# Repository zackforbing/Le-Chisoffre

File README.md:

# Le-Chisoffre

chiff riff with trackpad, mouseball or rotary support, now with hotswap

don't get mad at me if these don't work, they are untested. I have zero idea what I'm doing, and your yolo to jlc is not my problem

7/21/25 case probably complete. still have to prototype though. and export/upload the files. but hey pretty pictures

original readme preserved below

## Layout

[Link](https://www.keyboard-layout-editor.com/##@_name=Le%20Chisoffre&author=Ha%20Ha%20Ha%3B&@_y:2.5&x:5.95&a:7&w:1.25&h:1.25%3B&=%3B&@_r:10&rx:1&y:-0.09999999999999998&x:2&a:4%3B&=E%3B&@_y:-0.65&x:1%3B&=W&_x:1%3B&=R&=T%3B&@_y:-0.75%3B&=Q%3B&@_y:-0.6&x:2%3B&=D%3B&@_y:-0.6499999999999999&x:1%3B&=S&_x:1%3B&=F&=G%3B&@_y:-0.75%3B&=A%3B&@_y:-0.6000000000000001&x:2%3B&=C%3B&@_y:-0.6499999999999999&x:1%3B&=X&_x:1%3B&=V&=B%3B&@_y:-0.75%3B&=Z%3B&@_y:-0.6000000000000001&x:2&a:7&h:1.25%3B&=%3B&@_y:-0.6499999999999999&x:3&h:1.25%3B&=%3B&@_y:0.25&x:5&c=%239cffb2&h:1.5%3B&=%3B&@_y:-0.75&x:4&h:1.25%3B&=%3B&@_r:100&rx:5.25&ry:4&y:-1.1&x:-0.20000000000000018&c=%23f59595&w:1.5&w2:1.25&h2:2&x2:0.25%3B&=%3B&@_r:-100&rx:7.25&ry:4.87&y:-0.3200000000000003&x:-0.5099999999999998&w:1.5&w2:1.25&h2:2%3B&=%3B&@_r:-10&rx:7&ry:0.965&y:-0.20499999999999996&x:2.25&c=%23cccccc&a:4%3B&=I%3B&@_y:-0.6499999999999999&x:1.25%3B&=U&_x:1%3B&=O%3B&@_y:-0.9900000000000002&x:0.25%3B&=Y%3B&@_y:-0.76&x:4.25%3B&=P%3B&@_y:-0.6000000000000003&x:2.25%3B&=K%3B&@_y:-0.6499999999999999&x:1.25%3B&=J&_x:1%3B&=L%3B&@_y:-0.9899999999999998&x:0.25%3B&=H%3B&@_y:-0.7600000000000002&x:4.25%3B&=%2F:%0A%2F%3B%3B&@_y:-0.6000000000000001&x:2.25%3B&=%3C%0A,%3B&@_y:-0.6399999999999997&x:0.25%3B&=N&=M&_x:1%3B&=%3E%0A.%3B&@_y:-0.75&x:4.25%3B&=%3F%0A%2F%2F%3B&@_y:-0.6200000000000001&x:2.25&a:7&h:1.25%3B&=%3B&@_y:-0.6299999999999999&x:1.25&h:1.25%3B&=%3B&@_y:0.22999999999999954&x:-0.75&c=%239cffb2&h:1.5%3B&=%3B&@_y:-0.75&x:0.25&h:1.25%3B&=)

## Todo

- [ ] order & test pcb
- [ ] create firmware
- [x] create case

## Disclaimer

Please note that this project is a work in progress with no guarantees of a working outcome. No-one involved in this project is responsible for any usage issues that may arise. However, feel free to edit, modify and otherwise utilise these files.

## License

This project is released under the GPL v3 License. Please refer to the LICENCE file.

## Credits

As always big thanks to the many people who helped me and inspired this board!

Any questions, contact Calvin0563 on Discord.

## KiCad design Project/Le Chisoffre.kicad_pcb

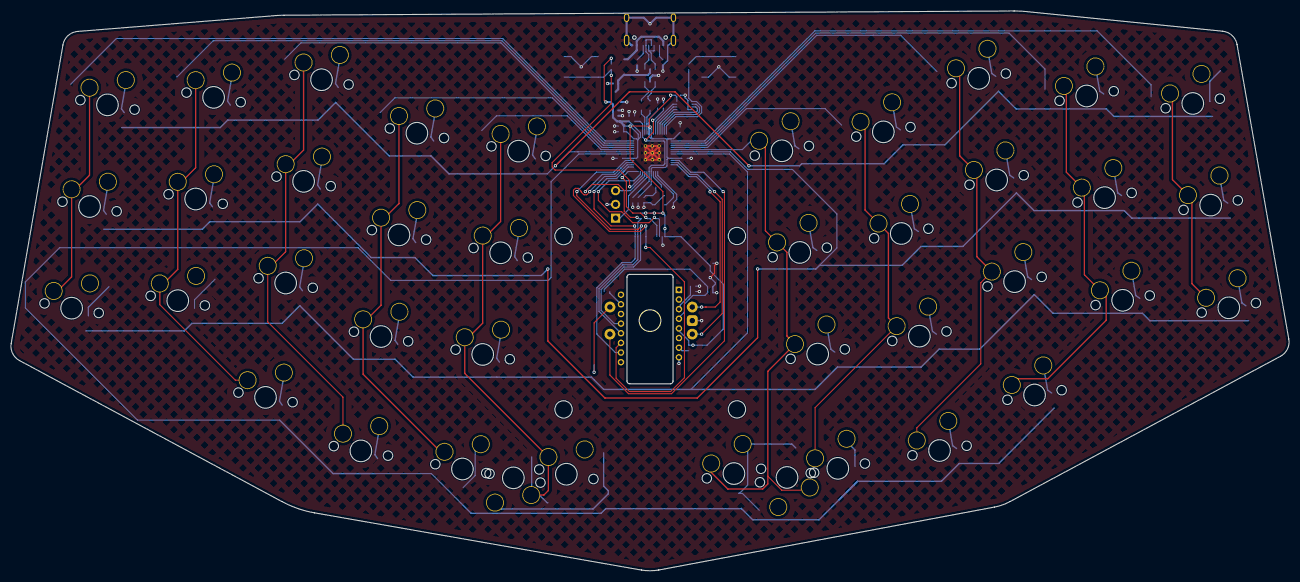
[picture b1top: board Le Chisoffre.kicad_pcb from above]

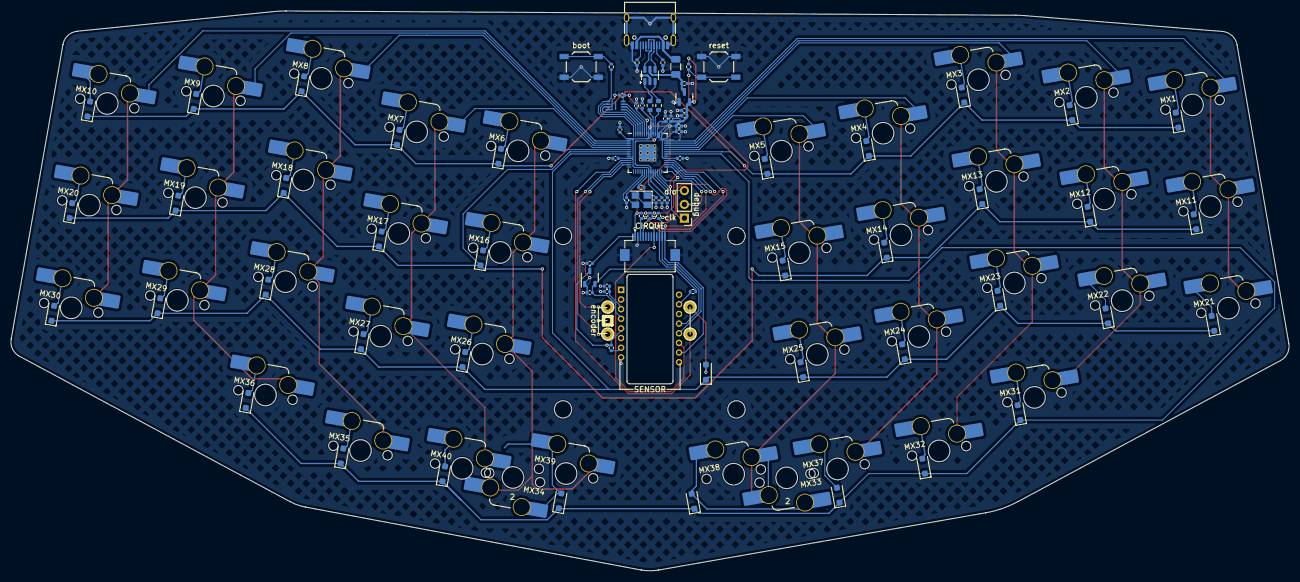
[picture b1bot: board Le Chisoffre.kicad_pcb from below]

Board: 2 copper layers, 235.8 x 103.3 mm, 130 parts (85 on the bottom side), 92 nets.

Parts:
C1, C5, C6, C9, C10, C11, C12, C13, C14, C15: 100nF; C_0402_1005Metric
C2, C3: 22pF; C_0402_1005Metric
C4, C8, C16, C17: 1uF; C_0402_1005Metric
C7: 10uF; C_0402_1005Metric
C18, C20, C21: 4u7; C_0402_1005Metric
C19: 100n; C_0402_1005Metric
D1, D2, D3, D4, D5, D6, D7, D8, D9, D10, D11, D12, D13, D14, D15, D16, D17, D18, D19, D20, D21, D22, D23, D24, D25, D26, D27, D28, D29, D30, D31, D32, D35, D36, D37, D38, D39, D40, D41: D_Small; D_SOD-123F
F1: 500mA; Fuse_1206_3216Metric
H1, H2, H3, H4: MountingHole; MountingHole_3.2mm_M3
IC1: W25Q16JVUXIQ; SON50P300X200X60-9N
J1: USB_C_Receptacle_USB2.0; USB_C_Receptacle_HRO_TYPE-C-31-M-12
J2: VIK Cirque Connector; VIK_Cirque_Horizontal
MX1, MX2, MX3, MX4, MX5, MX6, MX7, MX8, MX9, MX10, MX11, MX12, MX13, MX14, MX15, MX16, MX17, MX18, MX19, MX20, MX21, MX22, MX23, MX24, MX25, MX26, MX27, MX28, MX29, MX30, MX31, MX32, MX33, MX34, MX35, MX36, MX37, MX38, MX39, MX40: MX_SW_solder; SW_MX_HS_S_CPG151101S11_1u
R2, R6: 1k; R_0402_1005Metric
R3, R4: 5k1; R_0402_1005Metric
R5: 5.1k; R_0402_1005Metric
R7, R8: 27R; R_0603_1608Metric
R9, R11: 10k; R_0402_1005Metric
R10: 39; R_0402_1005Metric
R12, R13: 4k7; R_0402_1005Metric
SW1: boot; SW_SPST_TL3342
SW2: RotaryEncoder_Switch; ROT_Alps_EC11E-Switch
SWD1: Conn_01x03_Female; PinHeader_1x03_P2.54mm_Vertical
SWR1: Reset; SW_SPST_TL3342
U1: USBLC6-2SC6; SOT-23-6
U2: XC6206PxxxMR-Regulator_Linear; SOT-23
U3: RP2040; RP2040-QFN-56
U4: XC6206P202MR; SOT-23-3
U5: PMW3360DM-T2QU_1; PixArt_PMW3360DM-T2QU
Y1: 12MHz; Crystal_SMD_3225-4Pin_3.2x2.5mm

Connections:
+1V1: C4.1, C5.1, C6.1, U3.23 (DVDD), U3.45 (VREG_VOUT), U3.50 (DVDD)
+2V: C21.2, R10.2, U4.2 (VO), U5.4 (VDD)
+3V3: C1.1, C7.1, C8.1, C9.1, C10.1, C11.1, C12.1, C13.1, C14.1, C15.1, C17.2, C20.2, IC1.8 (VCC), J2.1 (3V3), R5.1, R9.2, R11.2, R12.1, R13.1, U2.2 (VO), U3.1 (IOVDD), U3.10 (IOVDD), U3.22 (IOVDD), U3.33 (IOVDD), U3.42 (IOVDD), U3.43 (ADC_AVDD), U3.44 (VREG_VIN), U3.48 (USB_VDD), U3.49 (IOVDD), U4.3 (VI), U5.5 (VDDIO)
+5V: C16.2, F1.2, U1.5 (VBUS), U2.3 (VI)
/CC1: J1.A5 (CC1), R3.1
/CC2: J1.B5 (CC2), R4.1
/D_+: R7.2, U3.47 (D+)
/D_-: R8.2, U3.46 (D-)
/QSPI_SCLK: IC1.6 (CLK), U3.52 (QSPI_SCLK)
/QSPI_SD0: IC1.5 (DI_IO0), U3.53 (QSPI_SD0)
/QSPI_SD1: IC1.2 (DO_IO1), U3.55 (QSPI_SD1)
/QSPI_SD2: IC1.3 (~WP_IO2), U3.54 (QSPI_SD2)
/QSPI_SD3: IC1.7 (~RESET_IO3), U3.51 (QSPI_SD3)
/QSPI_SS: IC1.1 (~CS), R2.1, U3.56 (QSPI_SS_N)
/XTAL_O: C3.2, R6.1, Y1.1
/~USB_BOOT: R2.2, SW1.2
COL0: MX1.1, MX11.1, MX21.1, U3.41 (GPIO29/ADC3)
COL1: MX2.1, MX12.1, MX22.1, MX31.1, U3.40 (GPIO28/ADC2)
COL2: MX3.1, MX13.1, MX23.1, MX32.1, U3.39 (GPIO27/ADC1)
COL3: MX4.1, MX14.1, MX24.1, MX37.1, U3.38 (GPIO26/ADC0)
COL4: MX5.1, MX15.1, MX25.1, MX33.1, MX38.1, U3.37 (GPIO25)
COL5: MX6.1, MX16.1, MX26.1, MX34.1, MX39.1, U3.6 (GPIO4)
COL6: MX7.1, MX17.1, MX27.1, MX40.1, U3.5 (GPIO3)
COL7: MX8.1, MX18.1, MX28.1, MX35.1, U3.4 (GPIO2)
COL8: MX9.1, MX19.1, MX29.1, MX36.1, U3.3 (GPIO1)
COL9: MX10.1, MX20.1, MX30.1, U3.2 (GPIO0)
COL10: SW2.S2, U3.11 (GPIO8)
CS: J2.10 (CS), U3.32 (GPIO21), U5.13 (NCS)
D_N: R8.1, U1.3 (I/O2)
D_P: R7.1, U1.1 (I/O1)
D_USB_N: J1.A7 (D-), J1.B7 (D-), U1.4 (I/O2)
D_USB_P: J1.A6 (D+), J1.B6 (D+), U1.6 (I/O1)
GND: C1.2, C2.1, C3.1, C4.2, C5.2, C6.2, C7.2, C8.2, C9.2, C10.2, C11.2, C12.2, C13.2, C14.2, C15.2, C16.1, C17.1, C18.2, C19.1, C20.1, C21.1, IC1.4 (GND), J1.A1 (GND), J1.A12 (GND), J1.B1 (GND), J1.B12 (GND), J1.S1 (SHIELD), J2.2 (GND), J2.MP, R3.2, R4.2, SW1.1, SW2.C, SWD1.2, SWR1.1 (A), U1.2 (GND), U2.1 (GND), U3.19 (TESTEN), U3.57 (GND), U4.1 (GND), U5.8 (GND), Y1.2, Y1.4
MISO: J2.11 (MISO), R11.1, U3.31 (GPIO20), U5.12 (MISO)
MOSI: J2.8 (MOSI), U3.30 (GPIO19), U5.11 (MOSI)
unnamed: D1.2 (A), MX1.2
unnamed: D2.2 (A), MX2.2
unnamed: D3.2 (A), MX3.2
unnamed: D4.2 (A), MX4.2
unnamed: D5.2 (A), MX5.2
unnamed: D6.2 (A), MX6.2
unnamed: D7.2 (A), MX7.2
unnamed: D8.2 (A), MX8.2
unnamed: D9.2 (A), MX9.2
unnamed: D10.2 (A), MX10.2
unnamed: D11.2 (A), MX11.2
unnamed: D12.2 (A), MX12.2
unnamed: D13.2 (A), MX13.2
unnamed: D14.2 (A), MX14.2
unnamed: D15.2 (A), MX15.2
unnamed: D16.2 (A), MX16.2
unnamed: D17.2 (A), MX17.2
unnamed: D18.2 (A), MX18.2
unnamed: D19.2 (A), MX19.2
unnamed: D20.2 (A), MX20.2
unnamed: D21.2 (A), MX21.2
unnamed: D22.2 (A), MX22.2
unnamed: D23.2 (A), MX23.2
unnamed: D24.2 (A), MX24.2
unnamed: D25.2 (A), MX25.2
unnamed: D26.2 (A), MX26.2
unnamed: D27.2 (A), MX27.2
unnamed: D28.2 (A), MX28.2
unnamed: D29.2 (A), MX29.2
unnamed: D30.2 (A), MX30.2
unnamed: D31.2 (A), MX31.2
unnamed: D32.2 (A), MX32.2
unnamed: D35.2 (A), MX35.2
unnamed: D36.2 (A), MX36.2
unnamed: D37.2 (A), MX37.2
unnamed: D38.2 (A), MX33.2, MX38.2
unnamed: D39.2 (A), MX34.2, MX39.2
unnamed: D40.2 (A), MX40.2
unnamed: D41.2 (A), SW2.S1
unnamed: R10.1, U5.15 (LED_P)
unnamed: R9.1, U5.7 (NRESET)
unnamed: C18.1, C19.2, U5.3 (VDDPIX)
ROW0: D1.1 (K), D2.1 (K), D3.1 (K), D4.1 (K), D5.1 (K), D6.1 (K), D7.1 (K), D8.1 (K), D9.1 (K), D10.1 (K), U3.36 (GPIO24)
ROW1: D11.1 (K), D12.1 (K), D13.1 (K), D14.1 (K), D15.1 (K), D16.1 (K), D17.1 (K), D18.1 (K), D19.1 (K), D20.1 (K), U3.7 (GPIO5)
ROW2: D21.1 (K), D22.1 (K), D23.1 (K), D24.1 (K), D25.1 (K), D26.1 (K), D27.1 (K), D28.1 (K), D29.1 (K), D30.1 (K), D41.1 (K), U3.8 (GPIO6)
ROW3: D31.1 (K), D32.1 (K), D35.1 (K), D36.1 (K), D37.1 (K), D38.1 (K), D39.1 (K), D40.1 (K), U3.35 (GPIO23)
SCK: J2.12 (SCK), U3.29 (GPIO18), U5.10 (SCLK)
SCL: J2.4 (SCL), R13.2, U3.28 (GPIO17)
SDA: J2.3 (SDA), R12.2, U3.27 (GPIO16)
SWCLK: SWD1.1, U3.24 (SWCLK)
SWD: SWD1.3, U3.25 (SWDIO)
VBUS: F1.1, J1.A4 (VBUS), J1.A9 (VBUS), J1.B4 (VBUS), J1.B9 (VBUS)
XTAL_IN: C2.2, U3.20 (XTAL_IN), Y1.3
XTAL_OUT: R6.2, U3.21 (XTAL_OUT)
rot_a: SW2.A, U3.12 (GPIO9)
rot_b: SW2.B, U3.13 (GPIO10)
~RESET: R5.2, SWR1.2 (B), U3.26 (~RUN)

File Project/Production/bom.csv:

Designator,Footprint,Quantity,Value,LCSC Part #
"C1, C10, C11, C12, C13, C14, C15, C5, C6, C9",0402,10,100nF,C1525
"C16, C17, C4, C8",0402,4,1uF,C52923
"C18, C20, C21",0402,3,4u7,C23733
C19,0402,1,100n,C307331
"C2, C3",0402,2,22pF,C1555
C7,0402,1,10uF,C15525
"D1, D10, D11, D12, D13, D14, D15, D16, D17, D18, D19, D2, D20, D21, D22, D23, D24, D25, D26, D27, D28, D29, D3, D30, D31, D32, D35, D36, D37, D38, D39, D4, D40, D41, D5, D6, D7, D8, D9",D_SOD-123F,39,D_Small,
F1,1206,1,500mA,C70076
IC1,SON50P300X200X60-9N,1,W25Q16JVUXIQ,C2843335
J1,USB_C_Receptacle_HRO_TYPE-C-31-M-12,1,USB_C_Receptacle_USB2.0,C165948
J2,VIK_Cirque_Horizontal,1,VIK Cirque Connector,C88360
"MX1, MX10, MX11, MX12, MX13, MX14, MX15, MX16, MX17, MX18, MX19, MX2, MX20, MX21, MX22, MX23, MX24, MX25, MX26, MX27, MX28, MX29, MX3, MX30, MX31, MX32, MX33, MX34, MX35, MX36, MX37, MX38, MX39, MX4, MX40, MX5, MX6, MX7, MX8, MX9",SW_MX_HS_S_CPG151101S11_1u,40,MX_SW_solder,
R10,0402,1,39,C25164
"R11, R9",0402,2,10k,C25744
"R12, R13",0402,2,4k7,C25900
R2,0402,1,1k,C25543
"R3, R4",0402,2,5k1,C25905
R5,0402,1,5.1k,
R6,0402,1,1k,C11702
"R7, R8",0603,2,27R,C25190
SW1,SW_SPST_TL3342,1,boot,C115351
SW2,ROT_Alps_EC11E-Switch,1,RotaryEncoder_Switch,
SWD1,PinHeader_1x03_P2.54mm_Vertical,1,Conn_01x03_Female,
SWR1,SW_SPST_TL3342,1,Reset,
U1,SOT-23-6,1,USBLC6-2SC6,C2827654
U2,SOT-23,1,XC6206PxxxMR-Regulator_Linear,C5446
U3,RP2040-QFN-56,1,RP2040,C2040
U4,SOT-23-3,1,XC6206P202MR,C2891260
U5,PixArt_PMW3360DM-T2QU,1,PMW3360DM-T2QU_1,
Y1,Crystal_SMD_3225-4Pin_3.2x2.5mm,1,12MHz,C9002

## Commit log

2025-03-22 wip update
2025-03-23 update
    first full version done
2025-03-23 clean up
2025-03-23 backup
2025-05-06 finalised
2025-06-17 pcb finalized, cleanup necessary
2025-06-18 added silk, new gerbs
2025-07-18 moved trackball, rerouted
2025-07-20 moved mcu, added extra encoder location
2025-07-20 missed connections
2025-07-21 clearing old files, symmetric edge cuts
2025-07-21 updated readme, added edge cuts for plate
2025-07-21 moved upper encoder down
2025-07-21 update readme, add proto screenshots
2025-07-21 update image links
2025-07-22 case
2025-08-03 moving things
